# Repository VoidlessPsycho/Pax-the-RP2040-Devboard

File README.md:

# Pax the RP2040 Devboard
Hello, my name is Voidless, and this is my first ever devboard using the RP2040 microcontroller. 

I made this project as part of the Blueprint YSWS for the Hack Club organization. I followed a guide on how to make a RP2040 Devboard using the KiCad PCB-making software. I wanted to learn more about electronics, and this project taught me about data flow, capacitors, resistors, and a whole bunch of electronics concepts.

**3D Models: ** \
 \
 \
 \

**PCB/Schematic: ** \
 \
 \

**BOM: ** \
 \

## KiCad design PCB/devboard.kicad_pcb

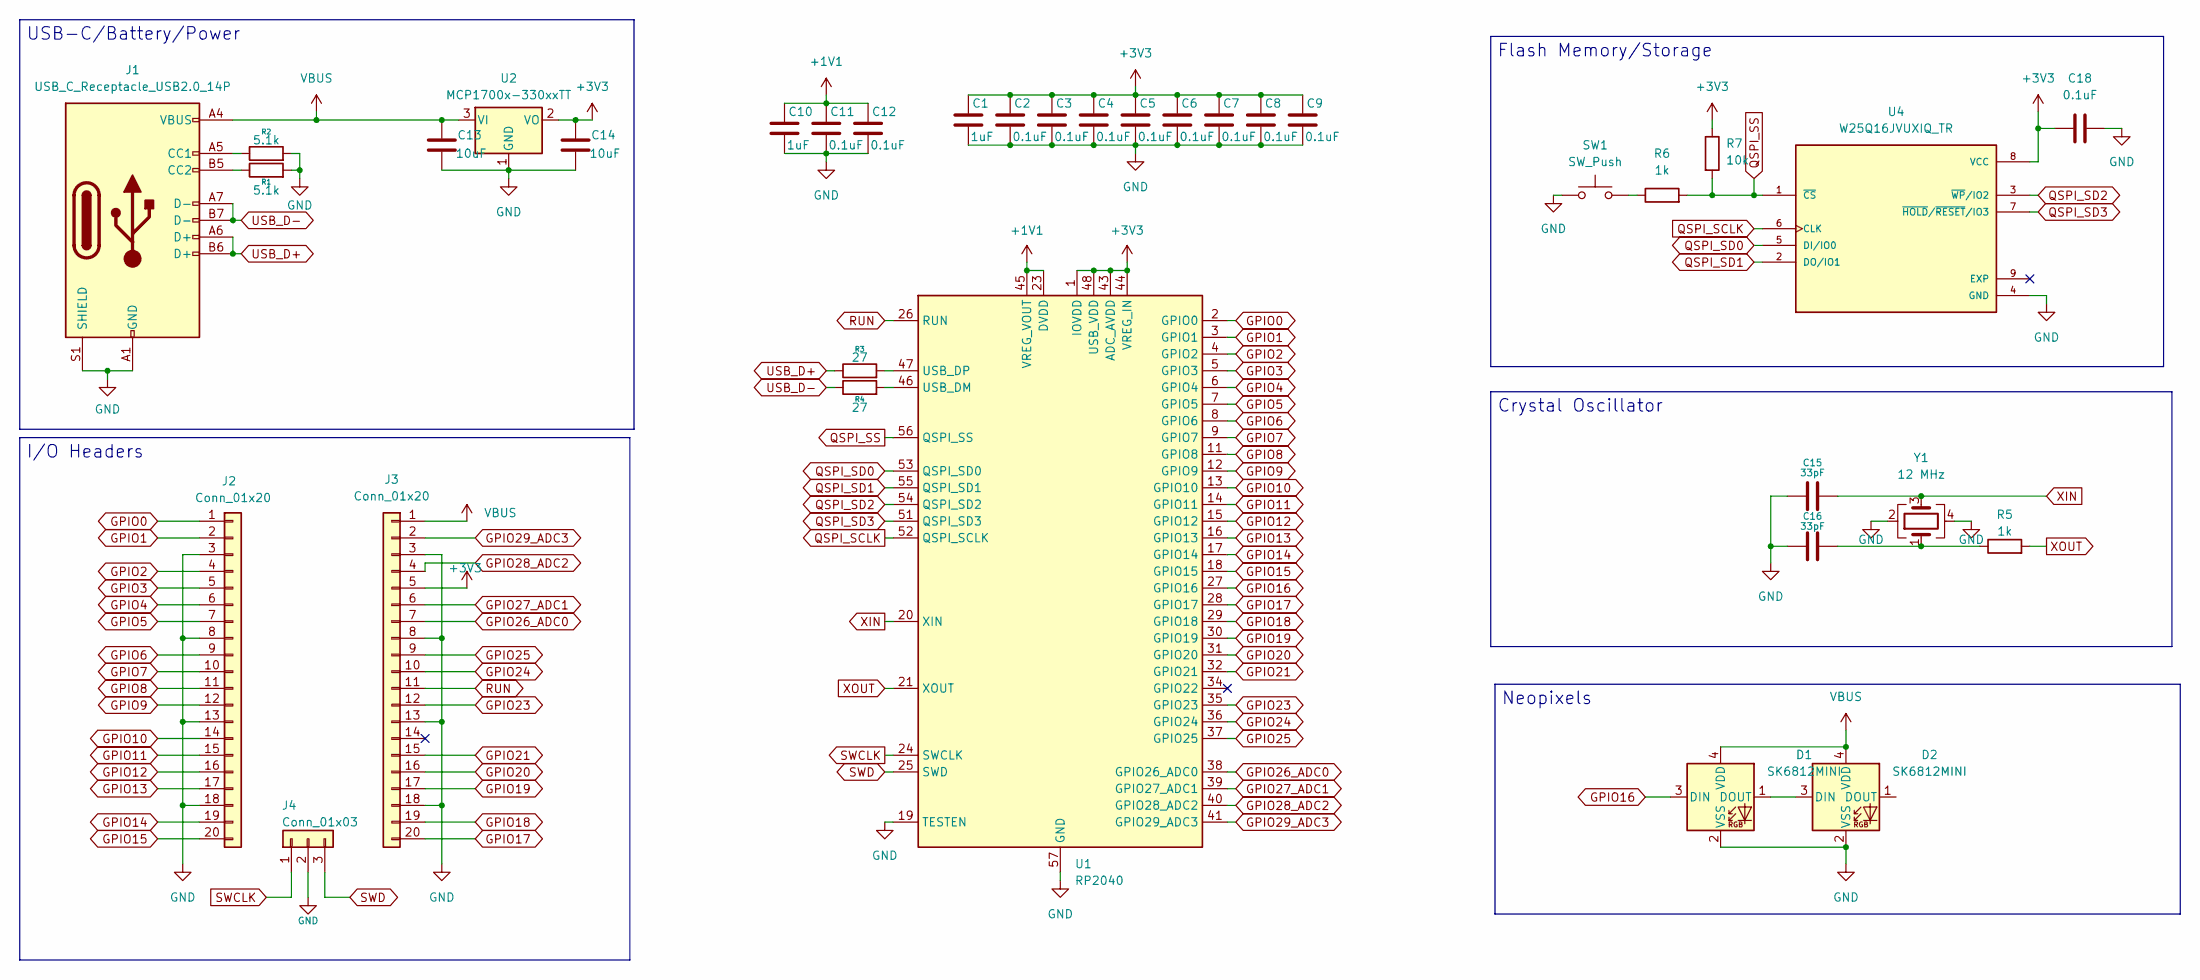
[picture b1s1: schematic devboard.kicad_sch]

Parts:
C1, C10: 1uF; C_0402_1005Metric
C2, C3, C4, C5, C6, C7, C8, C9, C11, C12, C18: 0.1uF; C_0402_1005Metric
C13, C14: 10uF; C_0603_1608Metric
C15, C16: 33pF; C_0402_1005Metric
D1, D2: SK6812MINI; LED_6028R
J1: USB_C_Receptacle_USB2.0_14P; USB_C_Receptacle_HRO_TYPE-C-31-M-12
J2, J3: Conn_01x20; PinHeader_1x20_P2.54mm_Vertical
J4: Conn_01x03; PinHeader_1x03_P2.54mm_Vertical
R1, R2: 5.1k; R_0402_1005Metric
R3, R4: 27; R_0402_1005Metric
R5, R6: 1k; R_0402_1005Metric
R7: 10k; R_0402_1005Metric
SW1: SW_Push; SW_Push_SPST_NO_Alps_SKRK
U1: RP2040; QFN-56-1EP_7x7mm_P0.4mm_EP3.2x3.2mm
U2: MCP1700x-330xxTT; SOT-23
U4: W25Q16JVUXIQ_TR; IC_W25Q16JVUXIQ_TR; PARTREV H
Y1: 12 MHz; Crystal_SMD_3225-4Pin_3.2x2.5mm

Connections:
+1V1: C10.1, C11.1, C12.1, U1.23 (DVDD), U1.45 (VREG_VOUT), U1.50 (DVDD)
+3V3: C1.1, C2.1, C3.1, C4.1, C5.1, C6.1, C7.1, C8.1, C9.1, C14.1, C18.2, J3.5, R7.1, U1.1 (IOVDD), U1.10 (IOVDD), U1.22 (IOVDD), U1.33 (IOVDD), U1.42 (IOVDD), U1.43 (ADC_AVDD), U1.44 (VREG_IN), U1.48 (USB_VDD), U1.49 (IOVDD), U2.2 (VO), U4.8 (VCC)
GND: C1.2, C2.2, C3.2, C4.2, C5.2, C6.2, C7.2, C8.2, C9.2, C10.2, C11.2, C12.2, C13.2, C14.2, C15.1, C16.1, C18.1, D1.2 (VSS), D2.2 (VSS), J1.A1 (GND), J1.A12 (GND), J1.B1 (GND), J1.B12 (GND), J1.S1 (SHIELD), J2.3, J2.8, J2.13, J2.18, J3.3, J3.8, J3.13, J3.18, J4.2, R1.2, R2.2, SW1.1, U1.19 (TESTEN), U1.57 (GND), U2.1 (GND), U4.4 (GND), Y1.2, Y1.4
GPIO0: J2.1, U1.2 (GPIO0)
GPIO1: J2.2, U1.3 (GPIO1)
GPIO2: J2.4, U1.4 (GPIO2)
GPIO3: J2.5, U1.5 (GPIO3)
GPIO4: J2.6, U1.6 (GPIO4)
GPIO5: J2.7, U1.7 (GPIO5)
GPIO6: J2.9, U1.8 (GPIO6)
GPIO7: J2.10, U1.9 (GPIO7)
GPIO8: J2.11, U1.11 (GPIO8)
GPIO9: J2.12, U1.12 (GPIO9)
GPIO10: J2.14, U1.13 (GPIO10)
GPIO11: J2.15, U1.14 (GPIO11)
GPIO12: J2.16, U1.15 (GPIO12)
GPIO13: J2.17, U1.16 (GPIO13)
GPIO14: J2.19, U1.17 (GPIO14)
GPIO15: J2.20, U1.18 (GPIO15)
GPIO16: D1.3 (DIN), U1.27 (GPIO16)
GPIO17: J3.20, U1.28 (GPIO17)
GPIO18: J3.19, U1.29 (GPIO18)
GPIO19: J3.17, U1.30 (GPIO19)
GPIO20: J3.16, U1.31 (GPIO20)
GPIO21: J3.15, U1.32 (GPIO21)
GPIO23: J3.12, U1.35 (GPIO23)
GPIO24: J3.10, U1.36 (GPIO24)
GPIO25: J3.9, U1.37 (GPIO25)
GPIO26_ADC0: J3.7, U1.38 (GPIO26_ADC0)
GPIO27_ADC1: J3.6, U1.39 (GPIO27_ADC1)
GPIO28_ADC2: J3.4, U1.40 (GPIO28_ADC2)
GPIO29_ADC3: J3.2, U1.41 (GPIO29_ADC3)
unnamed: C16.2, R5.1, Y1.1
unnamed: D1.1 (DOUT), D2.3 (DIN)
unnamed: J1.A5 (CC1), R2.1
unnamed: J1.B5 (CC2), R1.1
unnamed: R6.1, SW1.2
unnamed: R4.2, U1.46 (USB_DM)
unnamed: R3.2, U1.47 (USB_DP)
QSPI_SCLK: U1.52 (QSPI_SCLK), U4.6 (CLK)
QSPI_SD0: U1.53 (QSPI_SD0), U4.5 (DI/IO0)
QSPI_SD1: U1.55 (QSPI_SD1), U4.2 (DO/IO1)
QSPI_SD2: U1.54 (QSPI_SD2), U4.3 (~WP/IO2)
QSPI_SD3: U1.51 (QSPI_SD3), U4.7 (~HOLD/~RESET/IO3)
QSPI_SS: R6.2, R7.2, U1.56 (QSPI_SS), U4.1 (~CS)
RUN: J3.11, U1.26 (RUN)
SWCLK: J4.1, U1.24 (SWCLK)
SWD: J4.3, U1.25 (SWD)
USB_D+: J1.A6 (D+), J1.B6 (D+), R3.1
USB_D-: J1.A7 (D-), J1.B7 (D-), R4.1
VBUS: C13.1, D1.4 (VDD), D2.4 (VDD), J1.A4 (VBUS), J1.A9 (VBUS), J1.B4 (VBUS), J1.B9 (VBUS), J3.1, U2.3 (VI)
XIN: C15.2, U1.20 (XIN), Y1.3
XOUT: R5.2, U1.21 (XOUT)

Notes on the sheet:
USB-C/Battery/Power
Crystal Oscillator
Flash Memory/Storage
Neopixels
I/O Headers

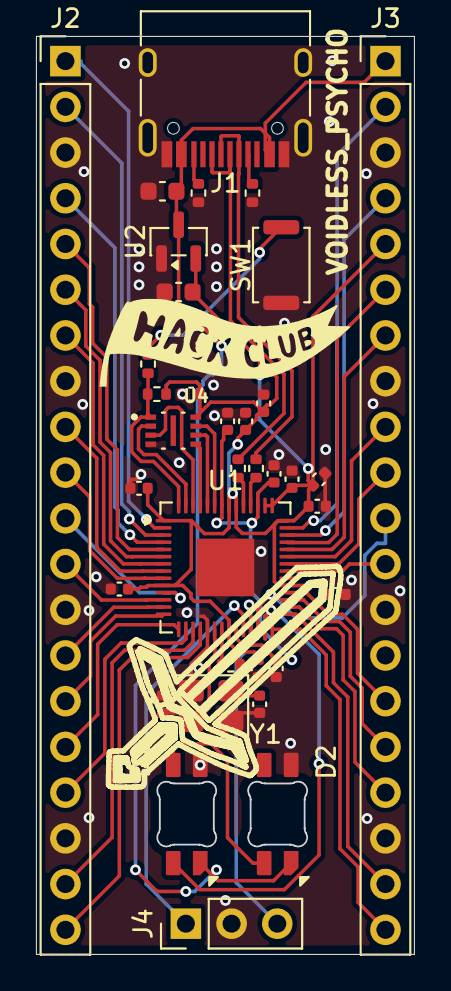
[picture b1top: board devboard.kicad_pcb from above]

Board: 2 copper layers, 20.9 x 51.0 mm, 35 parts (0 on the bottom side), 53 nets.

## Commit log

2025-12-03 Rename project from Voidless-Devboard to Pax the RP2040 Devboard
2025-12-03 Added CAD and PCB Folders
2025-12-03 Improve README formatting and section headers
    Updated formatting for sections and images in README.
2025-12-03 Fix formatting for schematic link in README
2025-12-03 Revise images and dimensions in README.md
    Updated image dimensions and added additional images for 3D models, PCB, and schematic.
